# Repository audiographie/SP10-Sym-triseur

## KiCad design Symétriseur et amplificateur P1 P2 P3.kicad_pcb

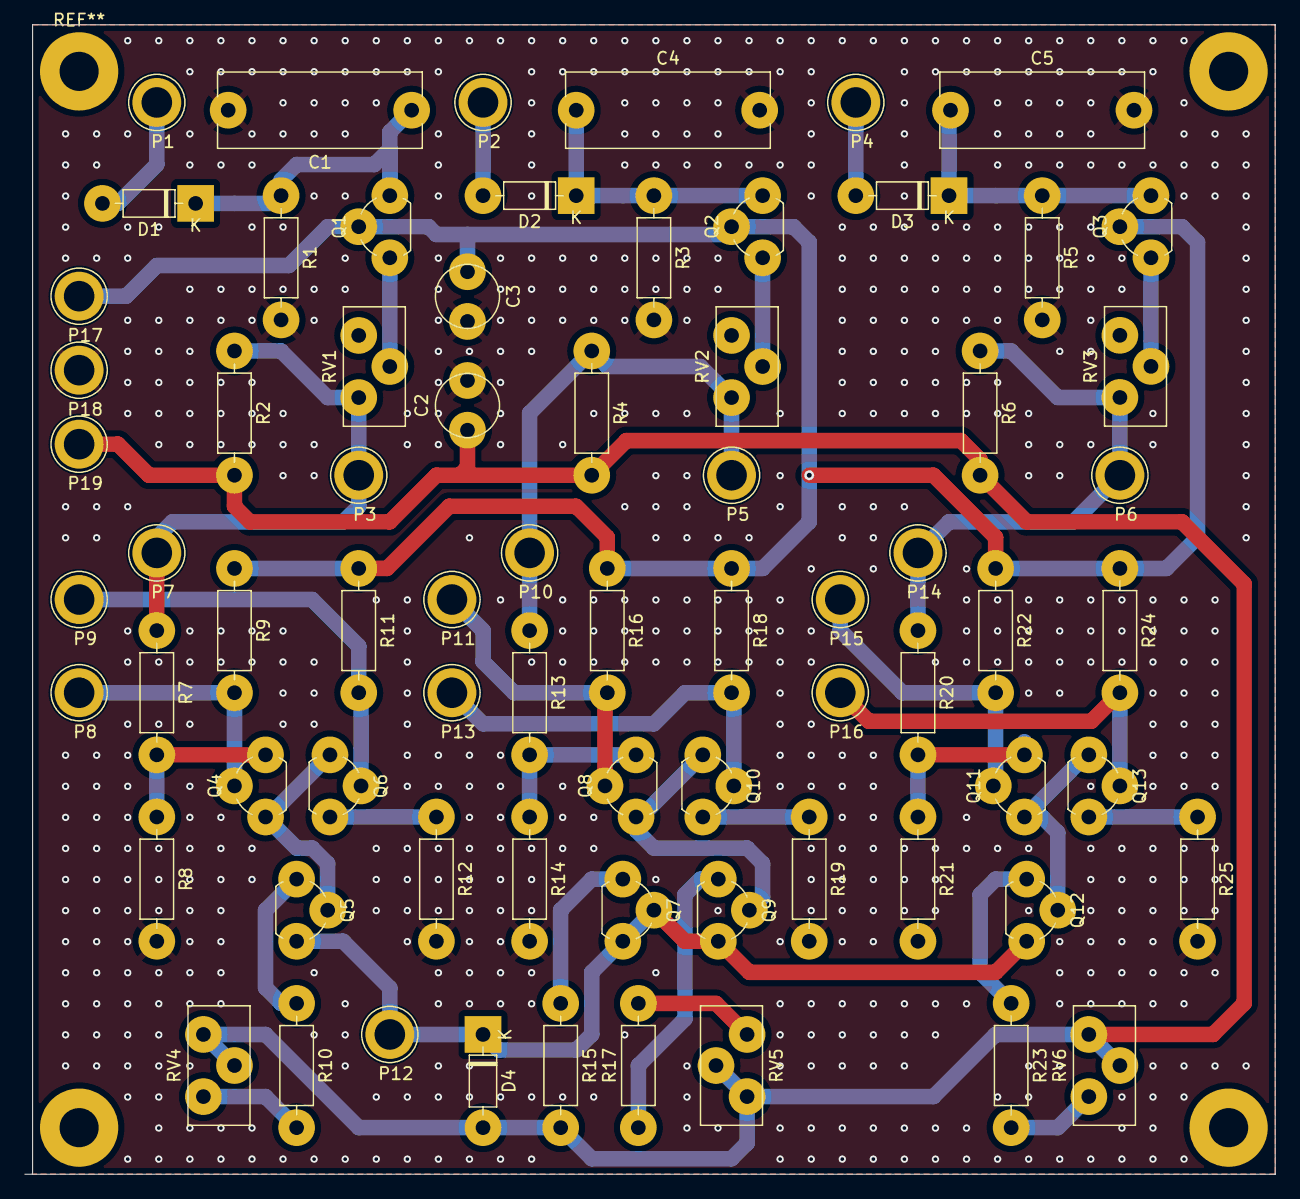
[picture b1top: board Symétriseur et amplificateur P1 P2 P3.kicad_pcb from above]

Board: 2 copper layers, 102.2 x 94.0 mm, 72 parts (0 on the bottom side), 38 nets.

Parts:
C1, C4, C5: 5100pF; C_Rect_L16.5mm_W6.0mm_P15.00mm_MKT
C2, C3: 10uF; C_Radial_D5.0mm_H11.0mm_P2.00mm
D1, D2, D3: D_Small; D_DO-35_SOD27_P7.62mm_Horizontal
D4: 1S1588; D_DO-35_SOD27_P7.62mm_Horizontal
P1, P17, P18, P19: P1; TestPoint_Loop_D3.80mm_Drill2.5mm
P2: P2; TestPoint_Loop_D3.80mm_Drill2.5mm
P3, P7: X1; TestPoint_Loop_D3.80mm_Drill2.5mm
P4: P3; TestPoint_Loop_D3.80mm_Drill2.5mm
P5, P10: X2; TestPoint_Loop_D3.80mm_Drill2.5mm
P6, P14: X3; TestPoint_Loop_D3.80mm_Drill2.5mm
P8: I1; TestPoint_Loop_D3.80mm_Drill2.5mm
P9: J1; TestPoint_Loop_D3.80mm_Drill2.5mm
P11: I2; TestPoint_Loop_D3.80mm_Drill2.5mm
P12: Y; TestPoint_Loop_D3.80mm_Drill2.5mm
P13: J2; TestPoint_Loop_D3.80mm_Drill2.5mm
P15: I3; TestPoint_Loop_D3.80mm_Drill2.5mm
P16: J3; TestPoint_Loop_D3.80mm_Drill2.5mm
Q1, Q2, Q3, Q4, Q5, Q6, Q7, Q8, Q9, Q10, Q11, Q12, Q13: 2SC2240; TO-92L_Wide
R1, R3, R5: 820k; R_Axial_DIN0207_L6.3mm_D2.5mm_P10.16mm_Horizontal
R2, R4, R6: 9.1k; R_Axial_DIN0207_L6.3mm_D2.5mm_P10.16mm_Horizontal
R7, R13, R20: 5.6K; R_Axial_DIN0207_L6.3mm_D2.5mm_P10.16mm_Horizontal
R8, R14, R21: 560; R_Axial_DIN0207_L6.3mm_D2.5mm_P10.16mm_Horizontal
R9, R11, R16, R18, R22, R24: 1k; R_Axial_DIN0207_L6.3mm_D2.5mm_P10.16mm_Horizontal
R10, R15, R17, R23: 100; R_Axial_DIN0207_L6.3mm_D2.5mm_P10.16mm_Horizontal
R12, R19, R25: 510; R_Axial_DIN0207_L6.3mm_D2.5mm_P10.16mm_Horizontal
RV1, RV2, RV3: 1k; Potentiometer_Bourns_3296Y_Vertical
RV4, RV5, RV6: 100; Potentiometer_Bourns_3296Y_Vertical

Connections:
/P1: D1.2 (A), P1.1
/P2: D2.2 (A), P2.1
/P3: D3.2 (A), P4.1
/VCC: C3.1, P17.1, Q1.2 (C), Q2.2 (C), Q3.2 (C), R9.1, R11.1, R16.1, R18.1, R22.1, R24.1
/VSS: C2.1, D4.2 (A), P19.1, R2.2, R4.2, R6.2, R15.2, RV4.1, RV4.2, RV5.1, RV5.2, RV6.1, RV6.2
/X1: P3.1, P7.1, R2.1, R7.1, RV1.3
/X2: P5.1, P10.1, R4.1, R13.1, RV2.3
/X3: P6.1, P14.1, R6.1, R20.1, RV3.3
/Y: D4.1 (K), P12.1, Q5.3 (B), Q7.2 (C), Q7.3 (B), Q9.3 (B), Q12.3 (B)
GND: C1.2, C2.2, C3.2, C4.2, C5.2, P18.1, R1.2, R3.2, R5.2, R8.2, R12.2, R14.2, R19.2, R21.2, R25.2
unnamed: C1.1, D1.1 (K), Q1.3 (B), R1.1
unnamed: C4.1, D2.1 (K), Q2.3 (B), R3.1
unnamed: C5.1, D3.1 (K), Q3.3 (B), R5.1
unnamed: P8.1, Q4.2 (C), R9.2
unnamed: P9.1, Q6.2 (C), R11.2
unnamed: P11.1, Q8.2 (C), R16.2
unnamed: P13.1, Q10.2 (C), R18.2
unnamed: P15.1, Q11.2 (C), R22.2
unnamed: P16.1, Q13.2 (C), R24.2
unnamed: Q1.1 (E), RV1.2
unnamed: Q2.1 (E), RV2.2
unnamed: Q3.1 (E), RV3.2
unnamed: Q4.3 (B), R7.2, R8.1
unnamed: Q4.1 (E), Q5.2 (C), Q6.1 (E)
unnamed: Q5.1 (E), R10.1
unnamed: Q6.3 (B), R12.1
unnamed: Q7.1 (E), R15.1
unnamed: Q8.3 (B), R13.2, R14.1
unnamed: Q9.1 (E), R17.1
unnamed: Q10.3 (B), R19.1
unnamed: Q8.1 (E), Q9.2 (C), Q10.1 (E)
unnamed: Q11.3 (B), R20.2, R21.1
unnamed: Q11.1 (E), Q12.2 (C), Q13.1 (E)
unnamed: Q12.1 (E), R23.1
unnamed: Q13.3 (B), R25.1
unnamed: R10.2, RV4.3
unnamed: R17.2, RV5.3
unnamed: R23.2, RV6.3

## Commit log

2025-11-04 Add files via upload
    Création du repo
2025-11-10 update
    update
